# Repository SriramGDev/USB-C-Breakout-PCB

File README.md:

# USB-C-Breakout-PCB
A simple USB-C breakout board meant to be used with mechanical keyboard PCBs. This DOES NOT use a JST connector, but rather a Molex one. It also does not use the standard Hirose Type-C port (which is prone to snapping off boards) but rather a more secure though more expensive hybrid SMT/THT Wurth port. See the BOM for more details.

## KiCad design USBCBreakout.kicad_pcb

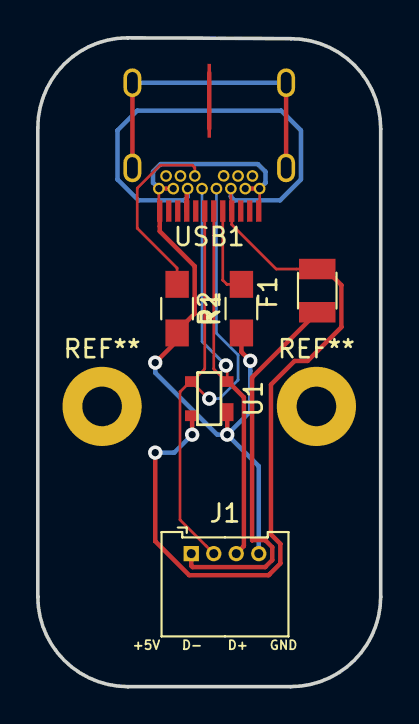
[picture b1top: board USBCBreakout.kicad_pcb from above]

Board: 2 copper layers, 19.1 x 36.0 mm, 6 parts (0 on the bottom side), 7 nets.

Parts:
F1: 500mA; Fuse_SMD1206_Reflow
J1: Conn_01x04; Molex_PicoBlade_53048-0410_04x1.25mm_Angled
R1, R2: 5.1k; R_0805_HandSoldering
U1: PRTR5V0U2X-ai03-locallib; SOT143B
USB1: Wurth-632723300011

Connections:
+5V: F1.1, J1.1
D+: J1.3, U1.2, USB1.6, USB1.18
D-: J1.2, U1.3, USB1.7, USB1.19
GND: J1.4, R1.1, R2.2, U1.1, USB1.1, USB1.12, USB1.13, USB1.24, USB1.25
unnamed: R1.2, USB1.5
unnamed: R2.1, USB1.17
VCC: F1.2, U1.4, USB1.4, USB1.9, USB1.16, USB1.21

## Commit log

2019-10-01 Initialized repo. Added current working breakout files.
2020-01-02 Generated gerbers.
2020-01-19 Made breakout slimmer, should accomodate much better panelling.
2020-01-19 .gitignore for KiCAD added.
2020-01-19 Create README.MD.
